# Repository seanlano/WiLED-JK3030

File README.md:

# WiLED: JK3030 LED board

Circuit board for up to six CREE JK3030 LEDs. To be used with a WiLED main board, which provides a 350 mA constant-current DC supply to the LEDs. The PCB is intended to be aluminium rather than FR4, and attached to a heatsink. 

# Licence

All hardware schematics and design files are released under the CERN Open Hardware Licence v1.2. Please see [LICENCE](LICENCE) for details.

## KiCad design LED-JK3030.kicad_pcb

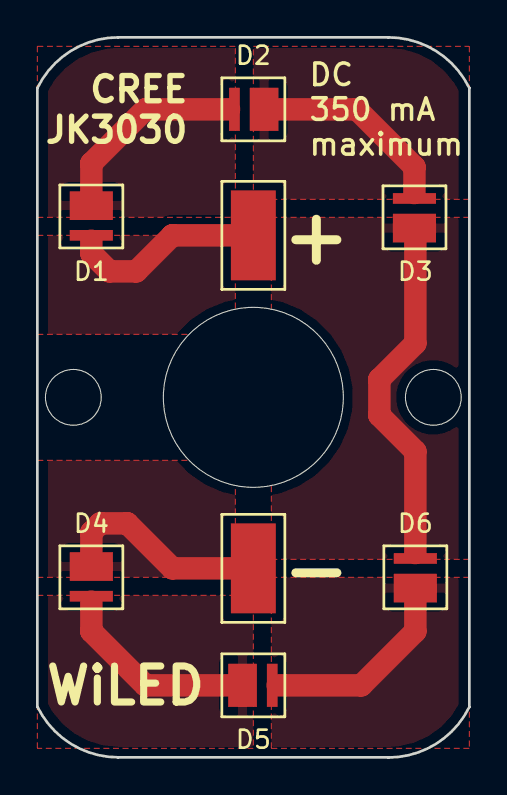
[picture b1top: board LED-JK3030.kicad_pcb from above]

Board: 2 copper layers, 24.0 x 40.0 mm, 8 parts (0 on the bottom side), 7 nets.

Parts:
D1, D2, D3, D4, D5, D6: JK3030
J1: +; 2x5mm_SMD_pad
J2: -; 2x5mm_SMD_pad

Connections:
unnamed: D1.1, D2.2
unnamed: D1.2, J1.1
unnamed: D2.1, D3.2
unnamed: D3.1, D6.2
unnamed: D4.1, J2.1
unnamed: D4.2, D5.1
unnamed: D5.2, D6.1

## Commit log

2018-07-01 Initial commit
    This first commit has a fully laid-out schematic and PCB, but may
    require changes after being reviewed.
2018-07-08 Final v1.0 layout
